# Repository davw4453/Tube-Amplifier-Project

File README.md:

# Tube-Amplifier-Project
This is a vacuum tube amplifier with modular input modules to provide for different audio source methods. This project was designed for my captsone project at CCSU.

# Design Requirements 
The design requirement files created as part of the CCSU capstone program are under the DesignRequirementDocs directory. The overall requirements definition is in RequirementsDefinition_DavidWrinn.odt. Each individual module of the system is defined in their respective hardware component specification file. 

# CAUTION
This project uses non-isolated high-voltage US mains power (120V). Be careful of electric shock when constructing and servicing. 

# Build Procedure
These are the steps to construct the project.

1. Have the mainboard and aux input module manufactured at your fab house of choice (JLCPCB, OshPark, etc.).

Mainboard Gerbers: EDAFiles/KiCAD_SCH/tubeAmp/gerbers/
Aux Module Gerbers: EDAFiles/KiCAD_SCH/auxModule/auxModule/gerbers/

2. Assemble the PCBs according to the component designators in the BOM: BOM/tubeAmp_BOM.ods

3. 3D print the case and lid. You can load tubecase.stl and tubecase-lid.3MF into a slicer and print in the material of choice. (I used BambuStudio and printed in clear PLA). The .3mf files are the BambuStudio project files. The .sldprt and .slddrw files are Solidworks CAD files as that is what application I used to design the case and lid. 

4. Mount the boards and components into the case. The mainboard is mounted on M3 standoffs with M3 screws. The lid also uses M3 screws. The speakers are affixed with M4-.70 x 16 screws. The input module should slice in place from the side.

5. Insert a 1A fuse into the power jack, plug in, and enjoy.

Pictures for reference can be found in the Pictures directory. 

# Problems 

- A list of problems can be found in problems.txt.
- Due to inrush current, I had to put an ICL thermistor inline from the main wall supply before the 170VDC rectifier. The part I used was: Vishay Ametherm SL1522102. https://www.digikey.com/en/products/detail/vishay-ametherm/SL1522102/1873476?s=N4IgTCBcDaIKwHYAMBaAygGQIxzGLSYKAcgCIgC6AvkA 
- In a future revision I hope to increase the supply voltage from 170VDC to 300VDC to allow for more power output. 

© 2026 David Wrinn. This work is licensed under CC BY-NC-SA 4.0

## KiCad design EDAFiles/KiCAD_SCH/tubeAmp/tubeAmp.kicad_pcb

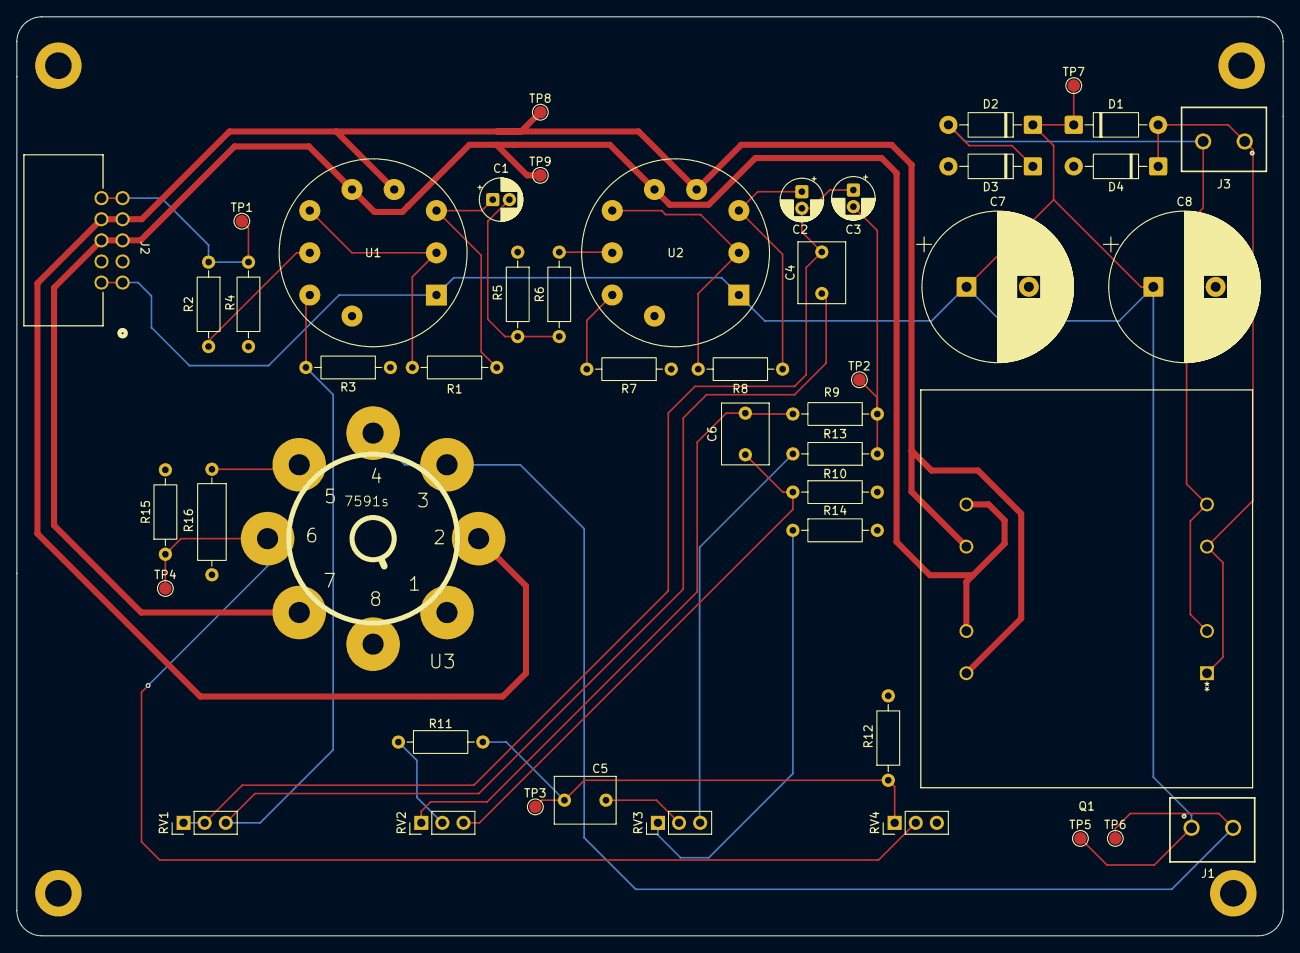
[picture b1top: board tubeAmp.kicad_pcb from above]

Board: 2 copper layers, 152.4 x 110.6 mm, 52 parts (0 on the bottom side), 28 nets.

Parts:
C1, C2, C3: 1u, 100V; CP_Radial_D5.0mm_P2.00mm
C4: 200p, 50V; C_Rect_L7.2mm_W5.5mm_P5.00mm_FKS2_FKP2_MKS2_MKP2
C5: 10n, 50V; C_Rect_L7.2mm_W5.5mm_P5.00mm_FKS2_FKP2_MKS2_MKP2
C6: 220n, 50V; C_Rect_L7.2mm_W5.5mm_P5.00mm_FKS2_FKP2_MKS2_MKP2
C7, C8: 470u, 200V; CP_Radial_D18.0mm_P7.50mm
D1, D2, D3, D4: 1N4004; D_DO-41_SOD81_P10.16mm_Horizontal
H1, H2, H3: MountingHole_3.2mm_M3_DIN965_Pad
H4: MountingHole_3.2mm_M3_DIN965_Pad
J1, J3: 691137710002; 691137710002-2screw
J2: 702471054; CONN_7024710xx_10pos
Q1: VPP12-800; TRANS_VPP12-800_TRM
R1, R2, R3, R6, R7, R8: 330, 1/4W; R_Axial_DIN0207_L6.3mm_D2.5mm_P10.16mm_Horizontal
R4, R12: 100K, 1/4W; R_Axial_DIN0207_L6.3mm_D2.5mm_P10.16mm_Horizontal
R5, R15: 560K, 1/4W; R_Axial_DIN0207_L6.3mm_D2.5mm_P10.16mm_Horizontal
R9, R10, R11: 2.2K, 1/4W; R_Axial_DIN0207_L6.3mm_D2.5mm_P10.16mm_Horizontal
R13, R14: 1K, 1/4W; R_Axial_DIN0207_L6.3mm_D2.5mm_P10.16mm_Horizontal
R16: 450, 1/2W; R_Axial_DIN0309_L9.0mm_D3.2mm_P12.70mm_Horizontal
RV1, RV2, RV3, RV4: 10K, 1/4W; PinHeader_1x03_P2.54mm_Vertical
TP1, TP2, TP3, TP4, TP5, TP6, TP7, TP8, TP9: TestPoint; TestPoint_Pad_D1.5mm
U1, U2: ECC88; Valve_Noval_P
U3: 7591s; OCTAL_CENTERHOLE

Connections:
AC+: D1.2 (A), D4.1 (K), J3.1, Q1.1, Q1.3 (4)
AC-: D2.2 (A), D3.1 (K), J3.2, Q1.2 (3), Q1.4 (6)
Aux_in: J2.5, J2.10, R2.1, R4.2, TP1.1
Filament+: J2.4, J2.9, Q1.6 (9), Q1.8 (12), TP8.1, U1.4 (F1), U2.4 (F1), U3.2 (F1)
Filament-: J2.3, J2.8, Q1.5 (7), Q1.7 (10), TP9.1, U1.5 (F2), U2.5 (F2), U3.7 (F2)
GND: C7.2, C8.2, D3.2 (A), D4.2 (A), H3.1, H4.1, J2.2, J2.7, R3.1, R4.1, R5.1, R7.1, R10.2, R12.2, R14.2, R15.2, R16.2, RV4.3
Line_out: C3.2, R9.1, R13.1, TP2.1
unnamed: C1.2, R5.2, R6.1
unnamed: C2.2, C3.1, C4.2, RV1.1, RV1.2
unnamed: C5.2, RV3.2
unnamed: C6.1, R9.2, RV2.1
unnamed: C6.2, R10.1, RV2.3
unnamed: R11.1, RV2.2
unnamed: R13.2, RV3.3
unnamed: R14.1, RV3.1
unnamed: R1.2, U1.2 (G), U1.6 (A)
unnamed: C1.1, R1.1, U1.3 (K)
unnamed: R2.2, U1.7 (G)
unnamed: C4.1, R3.2, RV1.3, U1.8 (K)
unnamed: R8.2, U2.2 (G), U2.6 (A)
unnamed: C2.1, R8.1, U2.3 (K)
unnamed: R6.2, U2.7 (G)
unnamed: R7.2, U2.8 (K)
unnamed: R16.1, U3.5 (F1)
Tone_out: C5.1, R11.2, R12.1, RV4.1, TP3.1
Vol_out: R15.1, RV4.2, TP4.1, U3.6 (G1)
xfmr+: C7.1, C8.1, D1.1 (K), D2.1 (K), J1.1, J2.1, J2.6, TP5.1, TP7.1, U1.1 (A), U2.1 (A)
xfmr-: J1.2, TP6.1, U3.3 (A), U3.4 (G2)

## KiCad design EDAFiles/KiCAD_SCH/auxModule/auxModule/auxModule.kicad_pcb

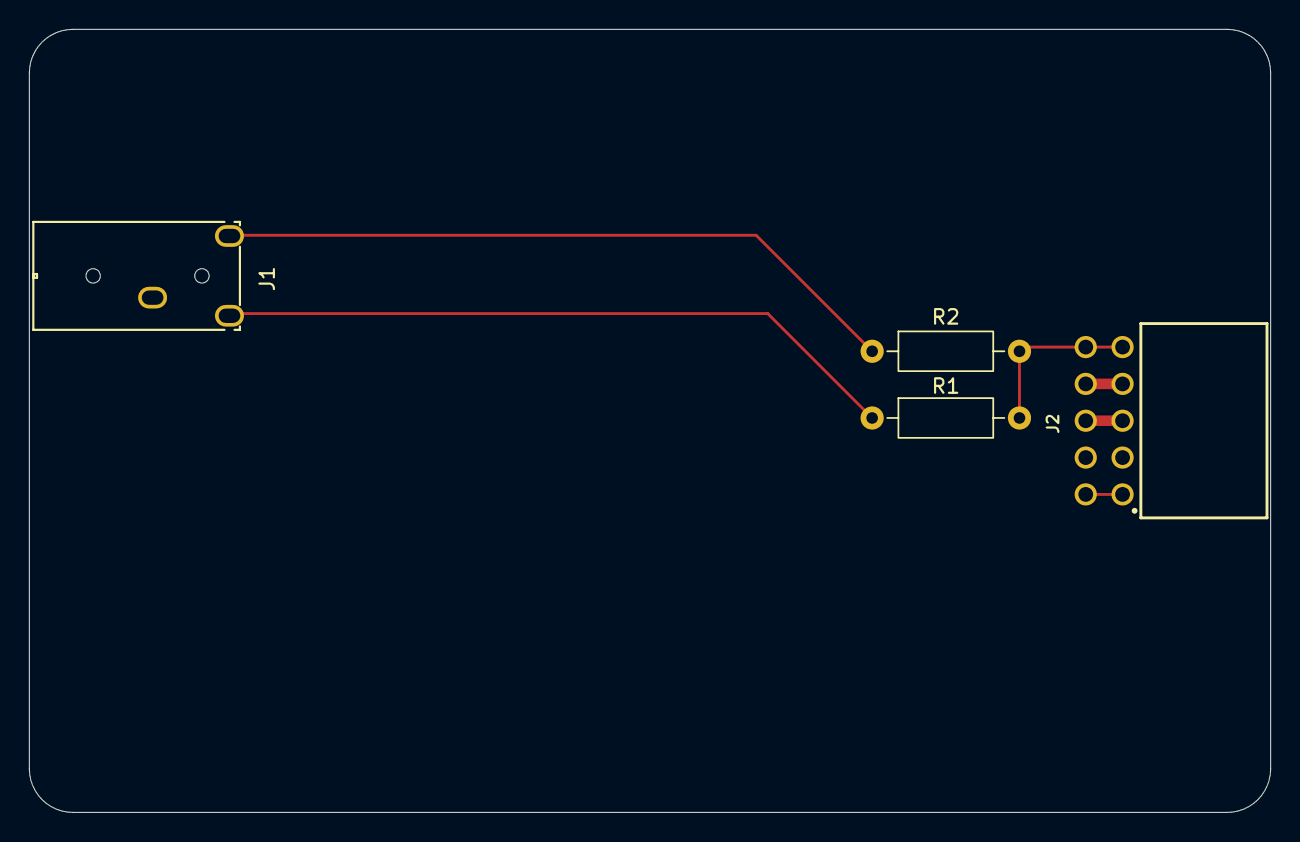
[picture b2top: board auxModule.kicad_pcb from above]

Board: 2 copper layers, 85.6 x 54.0 mm, 4 parts (0 on the bottom side), 7 nets.

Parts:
J1: STX-3000; STX-3000_KYC
J2: 6130XX243121_613010243121; 613010243121_10pin
R1, R2: 1K, 1/4W; R_Axial_DIN0207_L6.3mm_D2.5mm_P10.16mm_Horizontal

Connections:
GND: J1.1, J2.3, J2.4
unnamed: J1.2, R1.1
unnamed: J1.3, R2.1
unnamed: J2.9, J2.10, R1.2, R2.2
VPP: J2.1, J2.2
filament+: J2.7, J2.8
filament-: J2.5, J2.6

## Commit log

2025-12-19 Initial Upload
2026-02-27 Periodic Update from local Machine
2026-03-08 add problems.txt
2026-04-01 add LICENSE
2026-04-01 added copyright notice in Readme
2026-04-14 Add design requirement docs
2026-04-20 upload design calculations
2026-05-11 Added soundTesting.txt
2026-05-13 Documentation Updates
